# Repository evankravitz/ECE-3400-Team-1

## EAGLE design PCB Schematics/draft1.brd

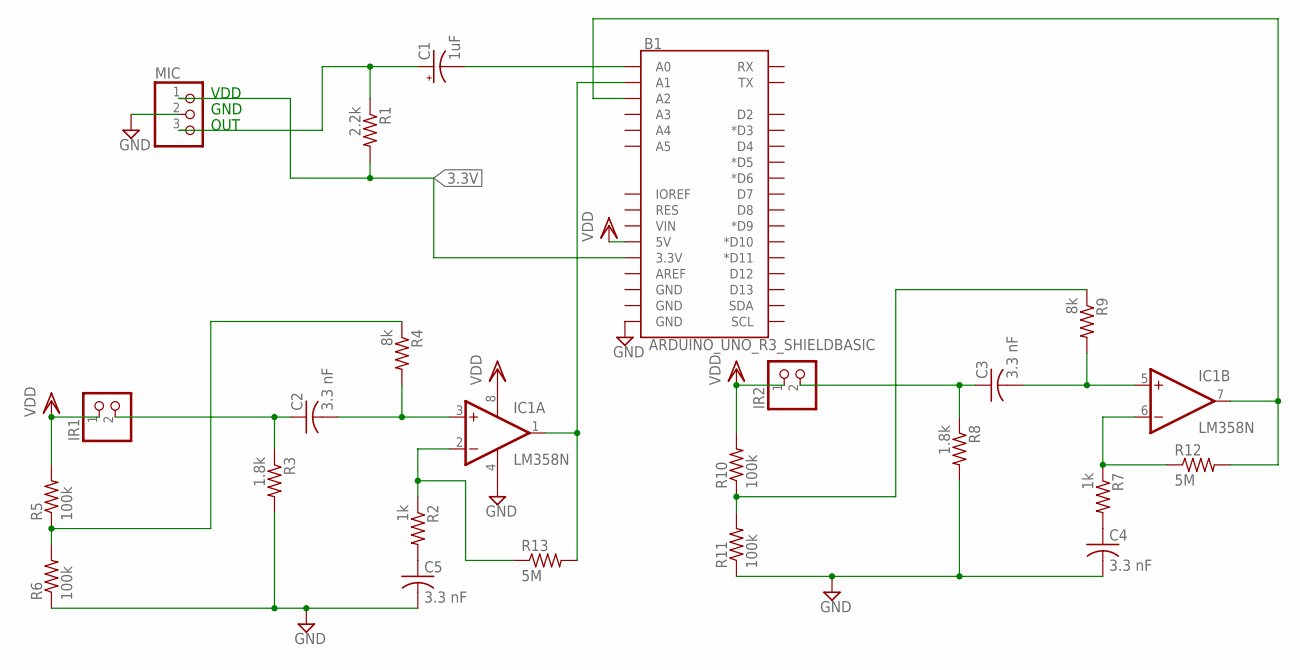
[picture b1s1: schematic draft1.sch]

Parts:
B1: ARDUINO_UNO_R3_SHIELDBASIC; UNO_R3_SHIELD
C1: 1uF; E5-6
C2, C3, C4, C5: 3.3 nF; C025-040X050
IC1: LM358N; DIL08
IR1, IR2: PINHD-1X2; 1X02
MIC: PINHD-1X3; 1X03
R1: 2.2k; 0207/7
R2, R7: 1k; 0207/7
R3, R8: 1.8k; 0207/7
R4, R9: 8k; 0207/7
R5, R6, R10, R11: 100k; 0207/7
R12, R13: 5M; 0207/7

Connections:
3.3V: B1.3.3V, MIC.1, R1.2
GND: B1.GND@0 (GND), C4.2, C5.2, IC1.4 (V-), MIC.2, R3.2, R6.1, R8.2, R11.1
unnamed: B1.A0, C1.-
unnamed: C1.+, MIC.3, R1.1
unnamed: B1.A2, IC1.7 (OUT), R12.2
unnamed: C4.1, R7.2
unnamed: C3.1, IR2.2, R8.1
unnamed: B1.A1, IC1.1 (OUT), R13.2
unnamed: C2.2, IC1.3 (+IN), R4.2
unnamed: IC1.6 (-IN), R7.1, R12.1
unnamed: C3.2, IC1.5 (+IN), R9.2
unnamed: IC1.2 (-IN), R2.1, R13.1
unnamed: R9.1, R10.1, R11.2
unnamed: R4.1, R5.1, R6.2
unnamed: C5.1, R2.2
unnamed: C2.1, IR1.2, R3.1
VDD: B1.5V, IC1.8 (V+), IR1.1, IR2.1, R5.2, R10.2

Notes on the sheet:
VDD
GND
OUT

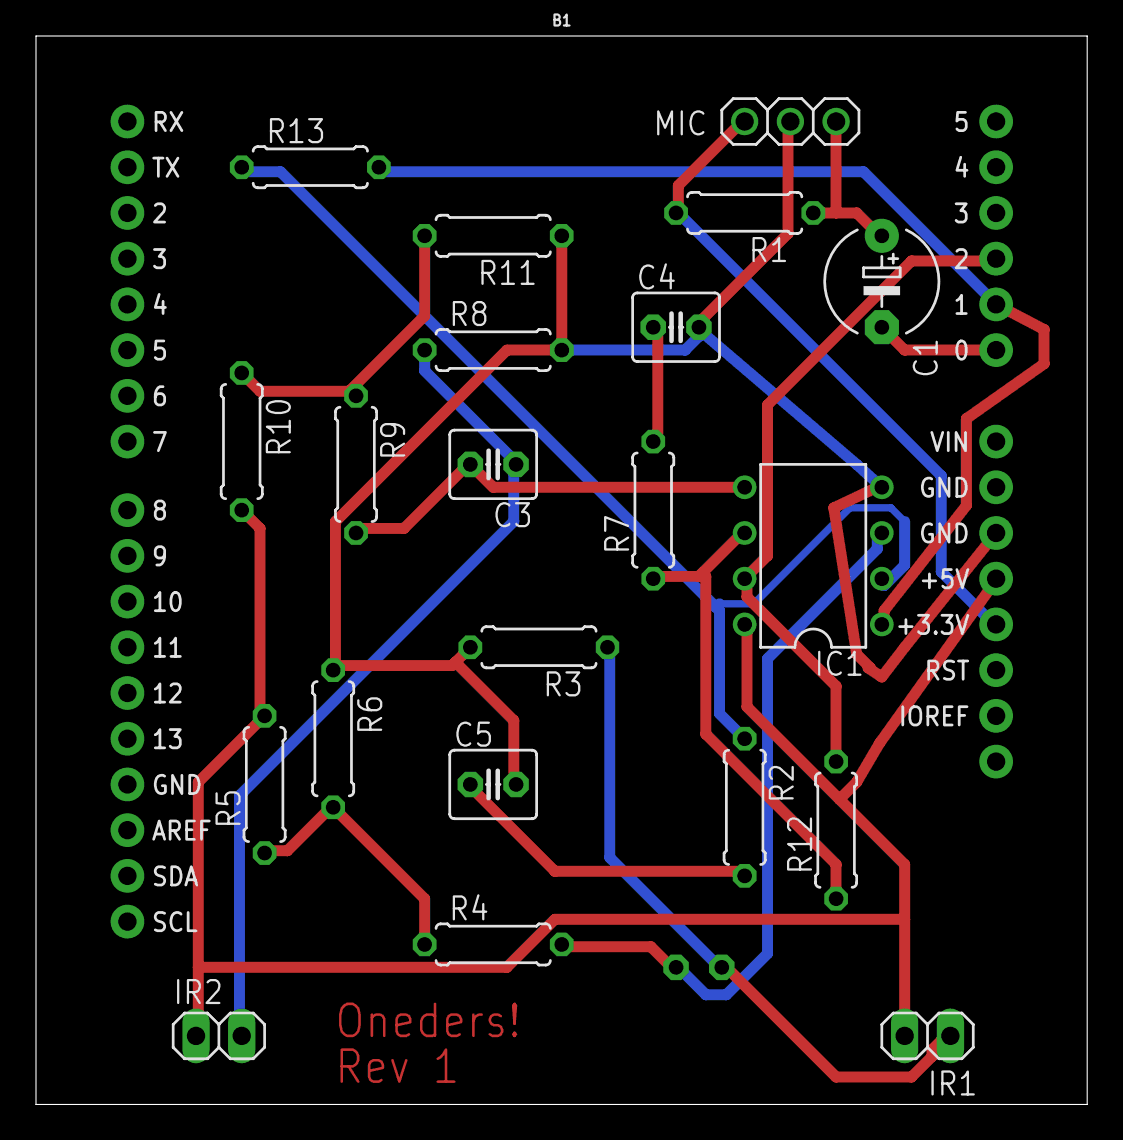
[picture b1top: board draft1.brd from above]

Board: 2 copper layers, 58.4 x 59.4 mm, 23 parts (1 on the bottom side), 17 nets.

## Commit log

2017-10-24 maze with gui
2017-10-28 fdxd
2017-10-30 code edits
2017-10-30 arduino edits
2017-11-03 fsm edits
2017-11-03 Create hello
2017-11-03 Rename lab1.md to past .md files/lab1.md
2017-11-03 Rename lab2.md to past .md files/lab2.md
2017-11-03 Rename lab3.md to past .md files/lab3.md
2017-11-03 Rename lab4.md to past .md files/lab4.md
2017-11-03 Rename milestone1.md to past .md files/milestone1.md
2017-11-03 Rename minutes.md to past .md files/minutes.md
2017-11-03 Rename Milestone2.md to past .md files/Milestone2.md
2017-11-04 rerter
2017-11-04 more updates
2017-11-04 ay ay
2017-11-04 fsdfds
2017-11-04 milestone4 updates
2017-11-04 m4 updates
2017-11-04 fsdfsdf
2017-11-04 sdada
2017-11-04 pic added
    hey
2017-11-04 more m4
2017-11-04 fdsfs
2017-11-04 fsdfsd
2017-11-05 fdsds
2017-11-05 fsm code
2017-11-05 m4 changes
    we da best
2017-11-05 new minutes
2017-11-05 chugging away
2017-11-05 sdfds
2017-11-05 almost final
2017-11-05 Update index.html
    formatting
2017-11-05 Update index.html
    formating
2017-11-06 finishing up m4
2017-11-06 final little bits
2017-11-06 video fix?
2017-11-06 system test
2017-11-06 robot fsm
2017-11-06 DFSMaze
2017-11-07 some edits
2017-11-07 final m3 edits
2017-11-07 i edited the website I think
2017-11-08 sdfsdf
2017-11-09 fdsfds
2017-11-09 sdfdsf
2017-11-09 jhgjh
2017-11-09 its 10 pm!!!
2017-11-10 meeting minutes!
2017-11-10 movement
2017-11-10 Left turn left wheel right turn right wheel
2017-11-10 making fpga moves
    hey hey
2017-11-12 ccxz
2017-11-13 Create WallSensorTest
2017-11-17 uhhh
2017-11-17 dhdgcv
2017-11-17 updated system test
2017-11-18 new changes.
2017-11-18 oeirh
2017-11-19 system test and fsm
2017-11-19 trash
2017-11-19 added new Junction Sensor code
2017-11-19 starting m4 writeup
2017-11-19 Revert "starting m4 writeup"
    This reverts commit 879ba9e9a7d9c0ffbea0be301ce478964c51ee47.
2017-11-19 Revert "Revert "starting m4 writeup""
    This reverts commit 5c839a24085d7fb41afd982c796722aa75f93712.
2017-11-19 m4 changes
2017-11-19 system test edits
2017-11-20 OG DFSIntegration
2017-11-20 Rename DFSIntegration.ino to OldDFSIntegration.ino
2017-11-20 OLD DFS
2017-11-20 efsgf
2017-11-20 gmhm
2017-11-20 wall transmission
2017-11-20 ewrhlwje
2017-11-20 report updates
2017-11-20 physical updates
2017-11-21 treasure detection
2017-11-21 treasure detection working!
2017-11-21 refactoring
2017-11-21 refactoring !!
2017-11-22 detecting treasures at front facing walls
2017-11-22 new changes
2017-11-22 jghghjjh
2017-11-22 lab write up tj
2017-11-22 final changes!!!
2017-11-27 adding youtube videos
2017-11-27 adding yt vids
2017-11-27 gvgh
2017-11-29 sdfsdfsd
2017-11-29 better start detection
2017-11-30 fdsfdsfsd
2017-11-30 since treasure won't be behind robot
2017-12-01 not much
2017-12-01 add good video
2017-12-01 done with navigation treasure detection
2017-12-01 fixed the broken thing
2017-12-02 meeting minutes
    get your meeting minutes here! hot and fresh out the oven
2017-12-02 made pictures smaller
2017-12-02 final design headers
2017-12-02 more edits
2017-12-02 fixed lab 2 videos
2017-12-02 working on the final page
2017-12-02 new video!
2017-12-02 more changes
2017-12-03 tryna get my vid to show up
2017-12-03 i figured it out I think
2017-12-03 started intro
2017-12-03 Create FINAL final robot code
2017-12-03 Create blah
2017-12-03 dsfdsf
2017-12-03 final final?
2017-12-04 intro!
2017-12-04 fixed everything being red
2017-12-04 FFT paragraph
2017-12-05 asdf
2017-12-05 microphone section
2017-12-05 high level algorithm stuff
2017-12-05 microphone pic?
2017-12-05 microphone size?
2017-12-05 ok finally fixed everything
2017-12-05 changed red text back to black
2017-12-05 making progress
2017-12-05 line follwing update
2017-12-05 conclusion done except for photos
2017-12-05 PICS!!!
2017-12-05 basestation pic
2017-12-05 more pictures
2017-12-05 turning
2017-12-05 protoboard stuff
2017-12-05 housekeeping
2017-12-05 finish physical robot
2017-12-06 arduino pins
2017-12-06 formatting fix
2017-12-06 sdfsd

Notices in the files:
parts and their libraries:
SparkFun-Boards: Licensing: Creative Commons ShareAlike 4.0 International - https://creativecommons.org/licenses/by-sa/4.0
